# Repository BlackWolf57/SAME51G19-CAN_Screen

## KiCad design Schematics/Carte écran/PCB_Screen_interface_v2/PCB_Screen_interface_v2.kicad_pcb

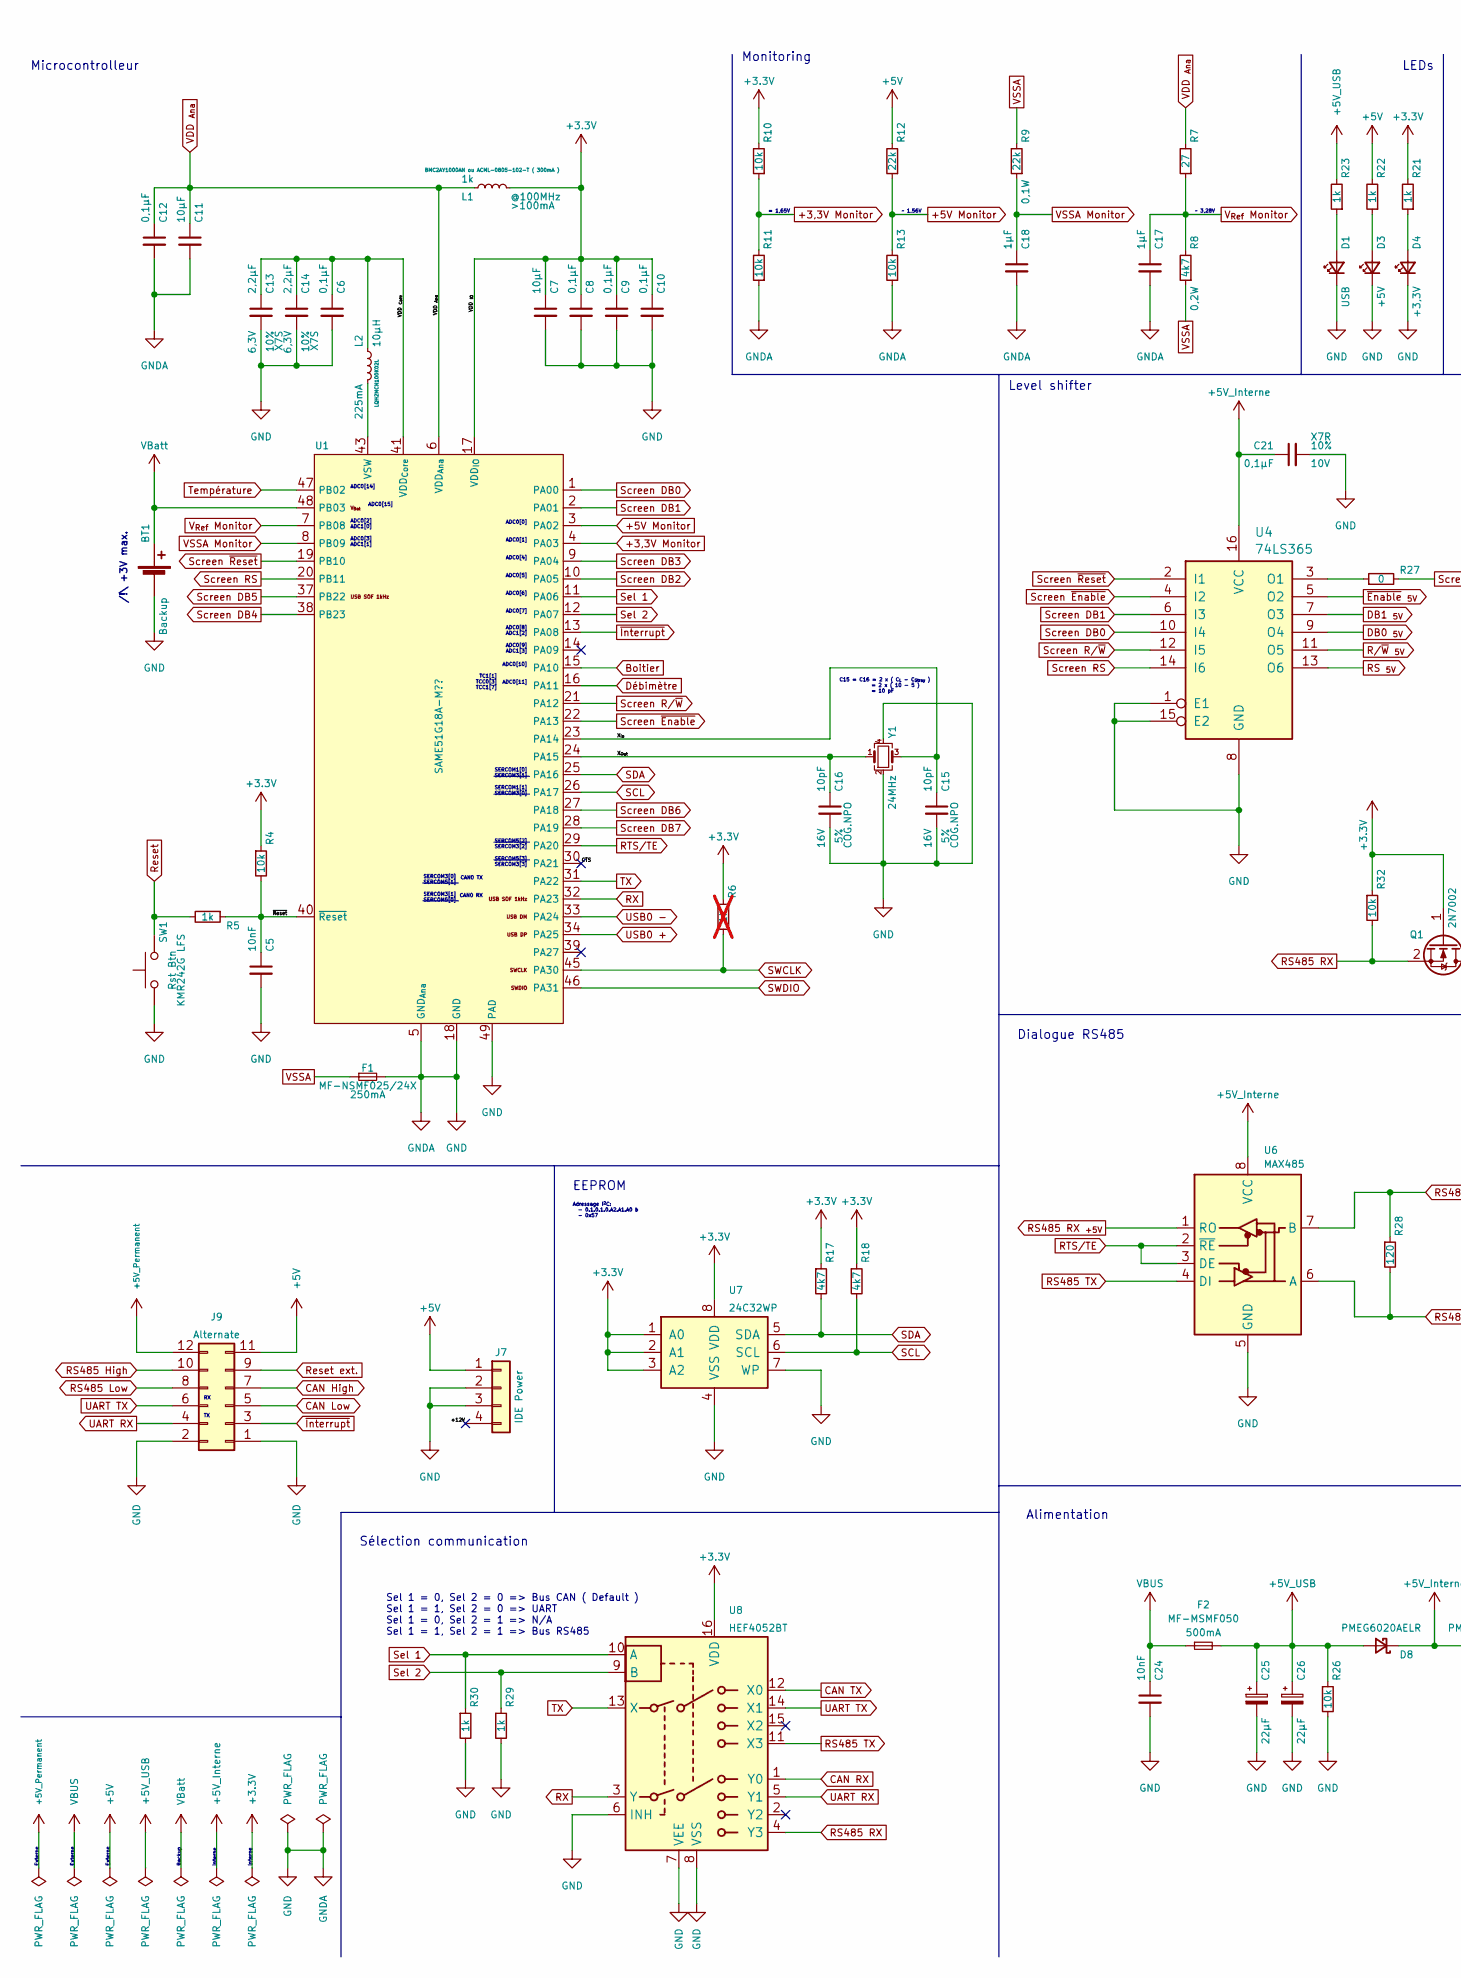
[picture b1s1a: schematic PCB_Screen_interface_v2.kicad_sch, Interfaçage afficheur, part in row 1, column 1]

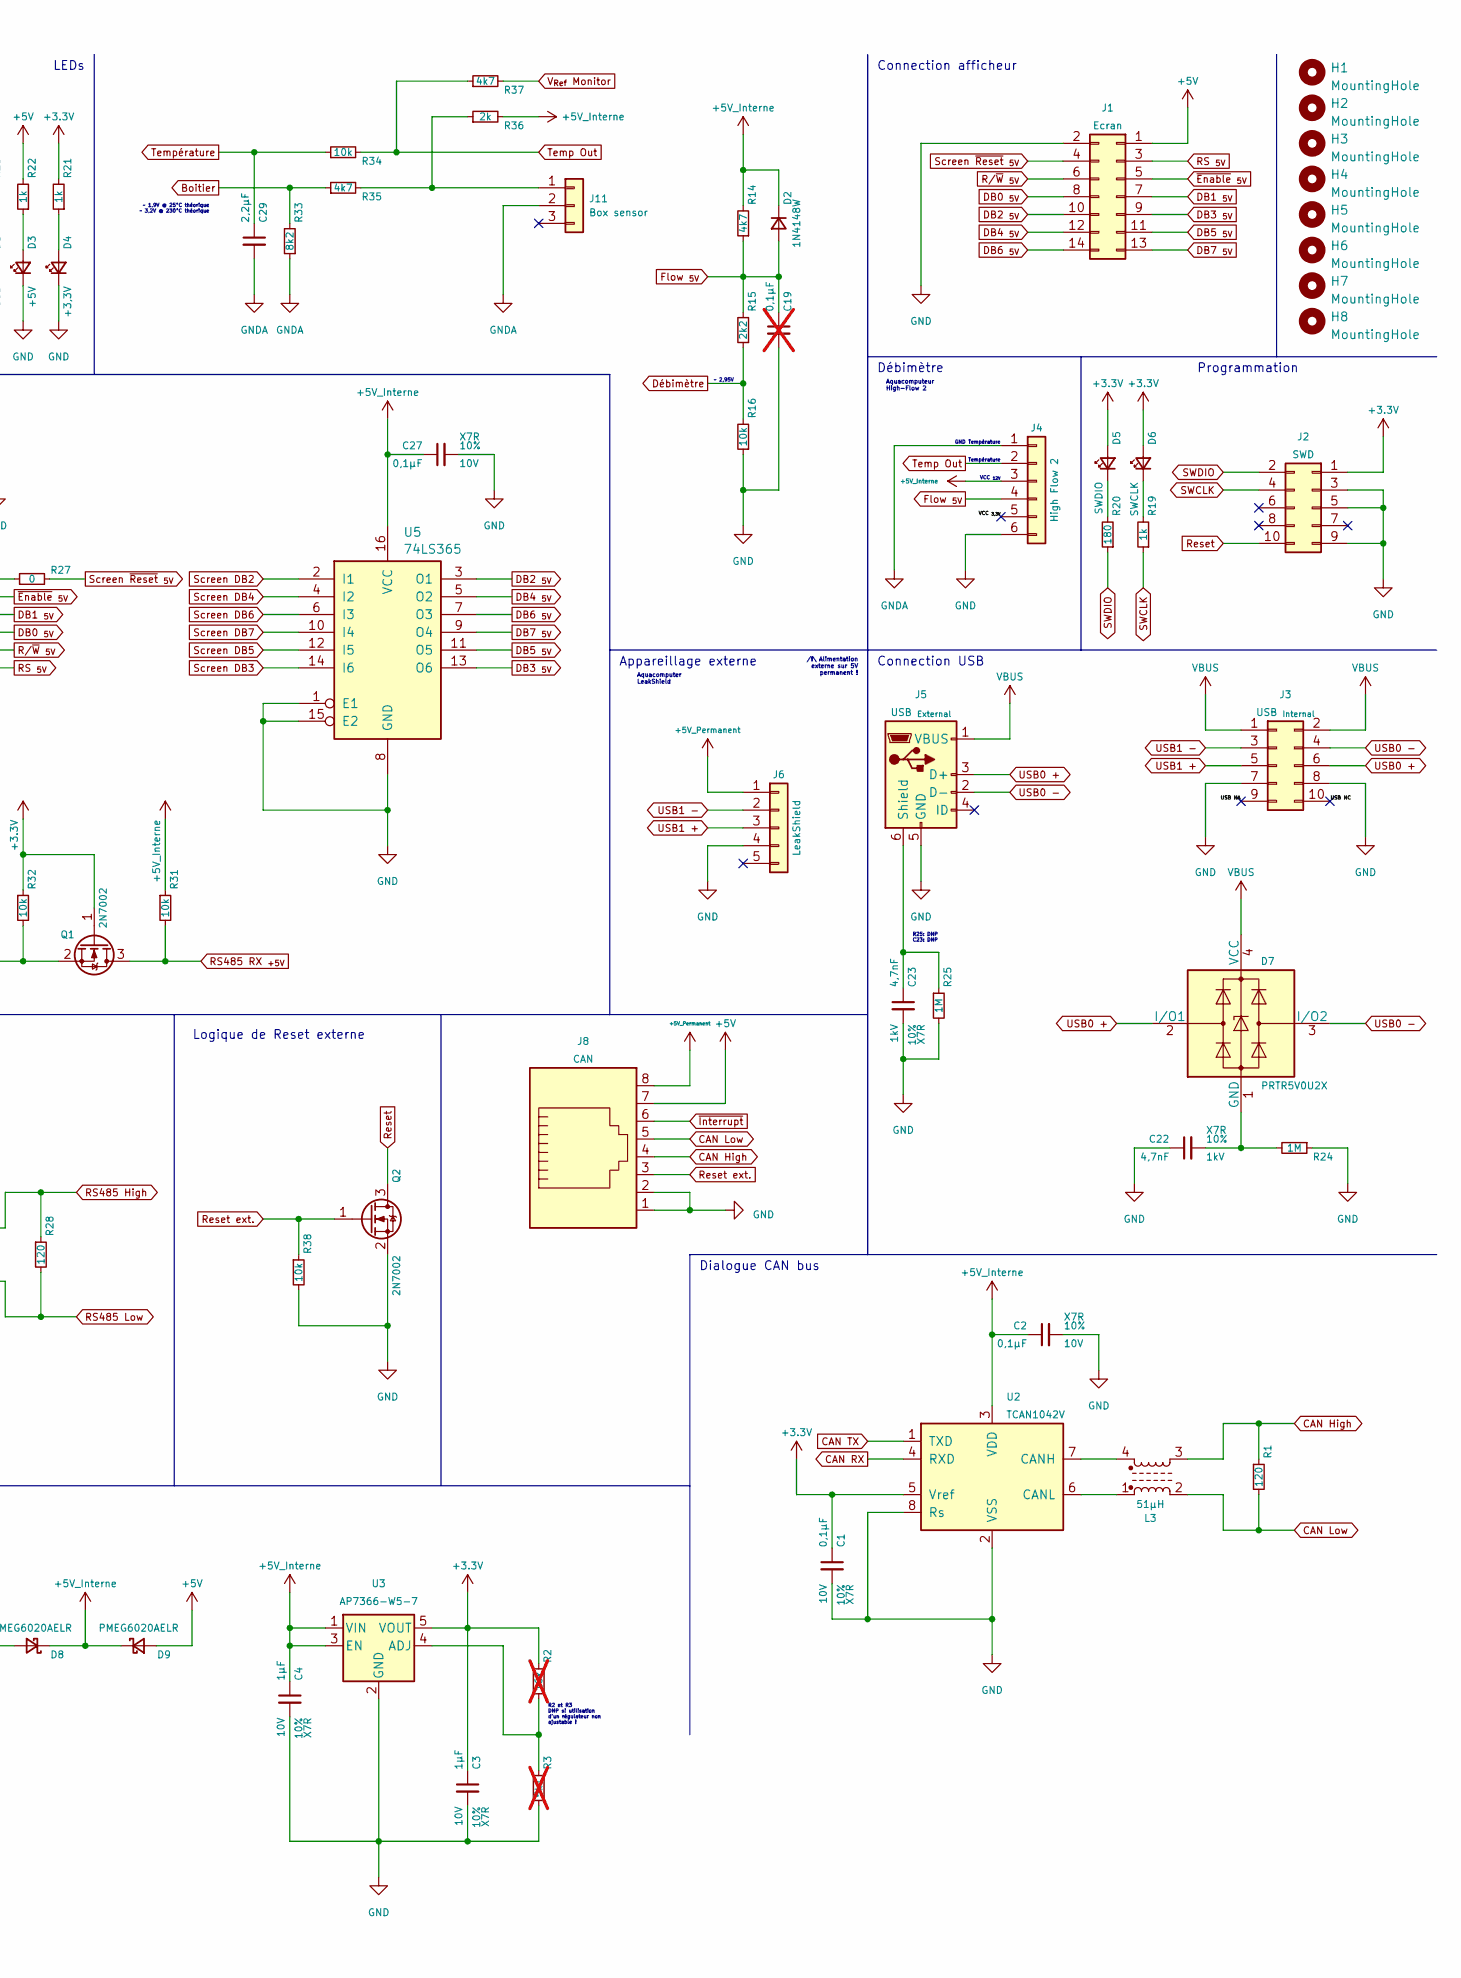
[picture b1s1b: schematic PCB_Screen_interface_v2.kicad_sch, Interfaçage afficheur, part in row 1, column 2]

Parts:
BT1: Backup; BatteryHolder_Keystone_106_1x20mm
C1, C2, C6, C8, C9, C10, C12, C21, C27: 0,1µF; C_0805_2012Metric
C3, C4, C17, C18: 1µF; C_0805_2012Metric
C5, C24: 10nF; C_0805_2012Metric
C7, C11: 10µF; C_0805_2012Metric
C13, C14, C29: 2,2µF; C_0805_2012Metric
C15, C16: 10pF; C_0805_2012Metric
C19: 0,1µF; C_0805_2012Metric; not fitted
C22, C23: 4,7nF; C_1206_3216Metric
C25, C26: 22µF; CP_Elec_4x5.8
D1: USB; LED_1206_3216Metric
D2: 1N4148W; D_SOD-123
D3: +5V; LED_1206_3216Metric_Pad1.42x1.75mm_HandSolder
D4: +3,3V; LED_1206_3216Metric_Pad1.42x1.75mm_HandSolder
D5: SWDIO; LED_1206_3216Metric
D6: SWCLK; LED_1206_3216Metric
D7: PRTR5V0U2X; SOT-143
D8, D9: PMEG6020AELR; Nexperia_CFP3_SOD-123W
F1: MF-NSMF025/24X; Fuse_1206_3216Metric
F2: MF-MSMF050; Fuse_1812_4532Metric
H1, H2, H3, H4, H5, H6, H7, H8: MountingHole; MountingHole_3.2mm_M3_DIN965
J1: Ecran; PinSocket_2x07_P2.54mm_Vertical
J2: SWD; PinHeader_2x05_P1.27mm_Vertical
J3: USB _{Internal}; IDC-Header_2x05_P2.54mm_Vertical
J4: High Flow 2; Molex_PicoBlade_53047-0610_1x06_P1.25mm_Vertical
J5: USB _{External}; Micro-USB
J6: LeakShield; Molex_PicoBlade_53047-0510_1x05_P1.25mm_Vertical
J7: IDE Power; Molex_4
J8: CAN; RJ45
J9: Alternate; IDC-Header_2x06_P2.54mm_Vertical
J11: Box sensor; Molex_PicoBlade_53047-0310_1x03_P1.25mm_Vertical
L1: 1k; L_0805_2012Metric
L2: 10µH; L_Murata_LQH2MCNxxxx02_2.0x1.6mm
L3: 51µH; Self_CAN
Q1, Q2: 2N7002; SOT-23
R1: 120; R_1206_3216Metric
R2: 16k; R_0805_2012Metric; not fitted
R3: 5k1; R_0805_2012Metric; not fitted
R4, R10, R11, R13, R16, R26, R31, R32, R34, R38: 10k; R_0805_2012Metric
R5, R19, R21, R22, R23, R29, R30: 1k; R_0805_2012Metric
R6: 1k; R_0805_2012Metric; not fitted
R7: 27; R_0805_2012Metric
R8: 4k7; R_1206_3216Metric
R9: 22k; R_1206_3216Metric
R12: 22k; R_0805_2012Metric
R14, R17, R18, R35, R37: 4k7; R_0805_2012Metric
R15: 2k2; R_0805_2012Metric
R20: 180; R_0805_2012Metric
R24, R25: 1M; R_0805_2012Metric
R27: 0; R_1206_3216Metric
R28: 120; R_0805_2012Metric
R33: 8k2; R_0805_2012Metric
R36: 2k; R_0805_2012Metric
SW1: Rst Btn; SW_Push_1P1T_NO_CK_KMR2
U1: SAME51G18A-M??; VQFN-48-1EP_7x7mm_P0.5mm_EP4.1x4.1mm
U2: TCAN1042V; SOIC-8_3.9x4.9mm_P1.27mm
U3: AP7366-W5-7; SOT-23-5
U4, U5: 74LS365; SOIC-16_3.9x9.9mm_P1.27mm
U6: MAX485; SOIC-8_3.9x4.9mm_P1.27mm
U7: 24C32WP; SOIC-8_3.9x4.9mm_P1.27mm
U8: HEF4052BT; SOIC-16_3.9x9.9mm_P1.27mm
Y1: 24MHz; Crystal_SMD_3225-4Pin_3.2x2.5mm

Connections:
+3,3V Monitor: R10.1, R11.2, U1.4 (PA03)
+3.3V: C1.1, C3.1, C7.1, C8.1, C9.1, C10.1, D5.2 (A), D6.2 (A), J2.1, L1.2, Q1.1 (G), R2.1, R4.1, R6.1, R10.2, R17.1, R18.1, R21.2, R32.1, U1.17 (VDD_{IO}), U1.36 (VDD_{IO}), U1.44 (VDD_{IO}), U2.5 (Vref), U3.5 (VOUT), U7.1 (A0), U7.2 (A1), U7.3 (A2), U7.8 (VDD), U8.16 (VDD)
+5V: D9.2 (A), J1.1, J7.1, J8.7, J9.11, R12.2, R22.2
+5V Monitor: R12.1, R13.2, U1.3 (PA02)
+5V_Interne: C2.1, C4.1, C21.1, C27.1, D2.1 (K), D8.1 (K), D9.1 (K), J4.3, R14.2, R31.1, R36.2, U2.3 (VDD), U3.1 (VIN), U3.3 (EN), U4.16 (VCC), U5.16 (VCC), U6.8 (VCC)
+5V_Permanent: J6.1, J8.8, J9.12
+5V_USB: C25.1, C26.1, D8.2 (A), F2.2, R23.2, R26.1
/+12V: J7.4
/CTS: U1.30 (PA21)
/USB NA: J3.9
/USB NC: J3.10
/VCC _{3,3V}: J4.5
/VDD _{Core}: C6.1, C13.1, C14.1, L2.1, U1.41 (VDD_{Core})
/X_{In}: C15.1, U1.23 (PA14), Y1.3
/X_{Out}: C16.1, U1.24 (PA15), Y1.1
/~Reset: C5.1, R4.2, R5.1, U1.40 (~Reset)
Boitier: R33.2, R35.1, U1.15 (PA10)
CAN High: J8.4, J9.7, L3.3, R1.1
CAN Low: J8.5, J9.5, L3.2, R1.2
CAN RX: U2.4 (RXD), U8.1 (Y0)
CAN TX: U2.1 (TXD), U8.12 (X0)
DB0 _{5V}: J1.8, U4.9 (O4)
DB1 _{5V}: J1.7, U4.7 (O3)
DB2 _{5V}: J1.10, U5.3 (O1)
DB3 _{5V}: J1.9, U5.13 (O6)
DB4 _{5V}: J1.12, U5.5 (O2)
DB5 _{5V}: J1.11, U5.11 (O5)
DB6 _{5V}: J1.14, U5.7 (O3)
DB7 _{5V}: J1.13, U5.9 (O4)
Débimètre: R15.1, R16.2, U1.16 (PA11)
Flow _{5V}: C19.1, D2.2 (A), J4.4, R14.1, R15.2
GND: BT1.2 (-), C1.2, C2.2, C3.2, C4.2, C5.2, C6.2, C7.2, C8.2, C9.2, C10.2, C11.2, C12.2, C13.2, C14.2, C15.2, C16.2, C17.2, C18.2, C19.2, C21.2, C22.1, C23.2, C24.2, C25.2, C26.2, C27.2, C29.2, D1.1 (K), D3.1 (K), D4.1 (K), F1.2, J1.2, J2.3, J2.5, J2.9, J3.7, J3.8, J4.1, J4.6, J5.5 (GND), J6.4, J7.2, J7.3, J8.1, J8.2, J9.1, J9.2, J11.2, Q2.2 (S), R3.2, R11.1, R13.1, R16.1, R24.1, R25.2, R26.2, R29.2, R30.2, R33.1, R38.2, SW1.1, U1.5 (GND_{Ana}), U1.18 (GND), U1.35 (GND), U1.42 (GND), U1.49 (PAD), U2.2 (VSS), U2.8 (Rs), U3.2 (GND), U4.1 (E1), U4.8 (GND), U4.15 (E2), U5.1 (E1), U5.8 (GND), U5.15 (E2), U6.5 (GND), U7.4 (VSS), U7.7 (WP), U8.6 (INH), U8.7 (VEE), U8.8 (VSS), Y1.2, Y1.4
unnamed: D1.2 (A), R23.1
unnamed: D3.2 (A), R22.1
unnamed: D4.2 (A), R21.1
unnamed: D5.1 (K), R20.2
unnamed: D6.1 (K), R19.2
unnamed: C22.2, D7.1 (GND), R24.2
unnamed: C23.1, J5.6 (Shield), R25.1
unnamed: J11.1, R35.2, R36.1
unnamed: L2.2, U1.43 (VSW)
unnamed: L3.4, U2.7 (CANH)
unnamed: L3.1, U2.6 (CANL)
unnamed: R2.2, R3.1, U3.4 (ADJ)
unnamed: R27.1, U4.3 (O1)
RS485 High: J9.10, R28.1, U6.7 (B)
RS485 Low: J9.8, R28.2, U6.6 (A)
RS485 RX: Q1.2 (S), R32.2, U8.4 (Y3)
RS485 RX _{+5V}: Q1.3 (D), R31.2, U6.1 (RO)
RS485 TX: U6.4 (DI), U8.11 (X3)
RS _{5V}: J1.3, U4.13 (O6)
RTS/TE: U1.29 (PA20), U6.2 (~RE), U6.3 (DE)
RX: U1.32 (PA23), U8.3 (Y)
Reset: J2.10, Q2.3 (D), R5.2, SW1.2
Reset ext.: J8.3, J9.9, Q2.1 (G), R38.1
R/~W _{5V}: J1.6, U4.11 (O5)
SCL: R18.2, U1.26 (PA17), U7.6 (SCL)
SDA: R17.2, U1.25 (PA16), U7.5 (SDA)
SWCLK: J2.4, R6.2, R19.1, U1.45 (PA30)
SWDIO: J2.2, R20.1, U1.46 (PA31)
Screen DB0: U1.1 (PA00), U4.10 (I4)
Screen DB1: U1.2 (PA01), U4.6 (I3)
Screen DB2: U1.10 (PA05), U5.2 (I1)
Screen DB3: U1.9 (PA04), U5.14 (I6)
Screen DB4: U1.38 (PB23), U5.4 (I2)
Screen DB5: U1.37 (PB22), U5.12 (I5)
Screen DB6: U1.27 (PA18), U5.6 (I3)
Screen DB7: U1.28 (PA19), U5.10 (I4)
Screen RS: U1.20 (PB11), U4.14 (I6)
Screen R/~W: U1.21 (PA12), U4.12 (I5)
Screen ~Enable: U1.22 (PA13), U4.4 (I2)
Screen ~Reset: U1.19 (PB10), U4.2 (I1)
Screen ~Reset _{5V}: J1.4, R27.2
Sel 1: R30.1, U1.11 (PA06), U8.10 (A)
Sel 2: R29.1, U1.12 (PA07), U8.9 (B)
TX: U1.31 (PA22), U8.13 (X)
Temp Out: J4.2, R34.2, R37.1
Température: C29.1, R34.1, U1.47 (PB02)
UART RX: J9.4, U8.5 (Y1)
UART TX: J9.6, U8.14 (X1)
USB0 +: D7.2 (I/O1), J3.6, J5.3 (D+), U1.34 (PA25)
USB0 -: D7.3 (I/O2), J3.4, J5.2 (D-), U1.33 (PA24)
USB1 +: J3.5, J6.3
USB1 -: J3.3, J6.2
VBUS: C24.1, D7.4 (VCC), F2.1, J3.1, J3.2, J5.1 (VBUS)
VBatt: BT1.1 (+), U1.48 (PB03)
VDD _{Ana}: C11.1, C12.1, L1.1, R7.2, U1.6 (VDD_{Ana})
VSSA: F1.1, R8.1, R9.2
VSSA Monitor: C18.1, R9.1, U1.8 (PB09)
V_{Ref} Monitor: C17.1, R7.1, R8.2, R37.2, U1.7 (PB08)
~Enable _{5V}: J1.5, U4.5 (O2)
~Interrupt: J8.6, J9.3, U1.13 (PA08)

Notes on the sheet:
ADC0[10]
SERCOM3[0] SERCOM5[1]
ADC0[3] ADC1[1]
ADC0[9] ADC1[3]
~ 3,28V
Connection afficheur
LEDs
Débimètre
SERCOM1[1] SERCOM3[0]
SERCOM5[2] SERCOM3[2]
GND Température
= 1,65V
EEPROM
Externe
ADC0[2] ADC1[0]
CAN0 RX
ADC0[4]
Level shifter
Dialogue CAN bus
Alimentation
Adressage I^{2}C: - 0.1.0.1.0.A2.A1.A0 b - 0x57
Appareillage externe
Interne
Backup
Monitoring
ADC0[14]
~ 1,9V @ 25°C théorique ~ 3,2V @ 230°C théorique
Sélection communication
ADC0[7]
CAN0 TX
Programmation
ADC0[1]
/!\ Alimentation externe sur 5V permanent !
R25: DNP C23: DNP
/!\ +3V max.
C15 = C16 = 2 x ( C_{L} - C_{Stray} ) = 2 x ( 10 - 5 ) = 10 pF
Microcontrolleur
ADC0[15]
TC1[1] TCC0[3] TCC1[7]
ADC0[6]

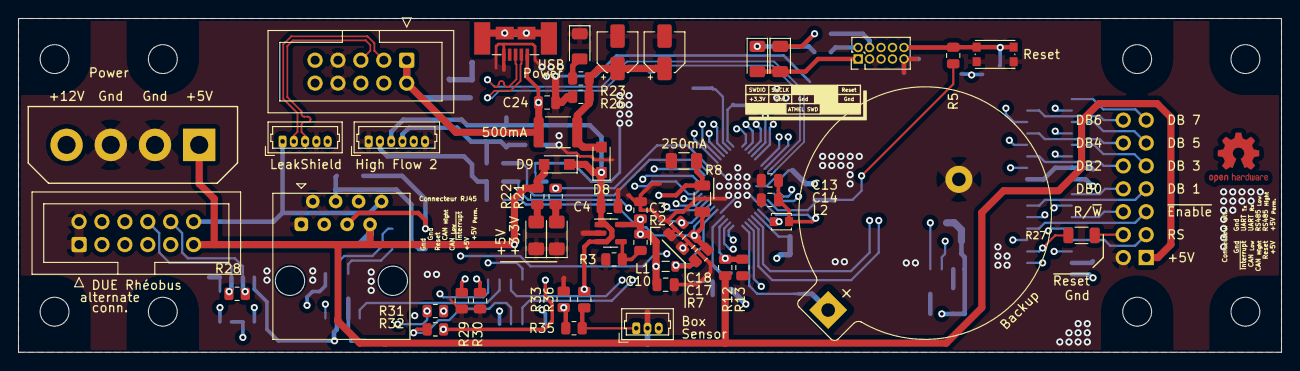
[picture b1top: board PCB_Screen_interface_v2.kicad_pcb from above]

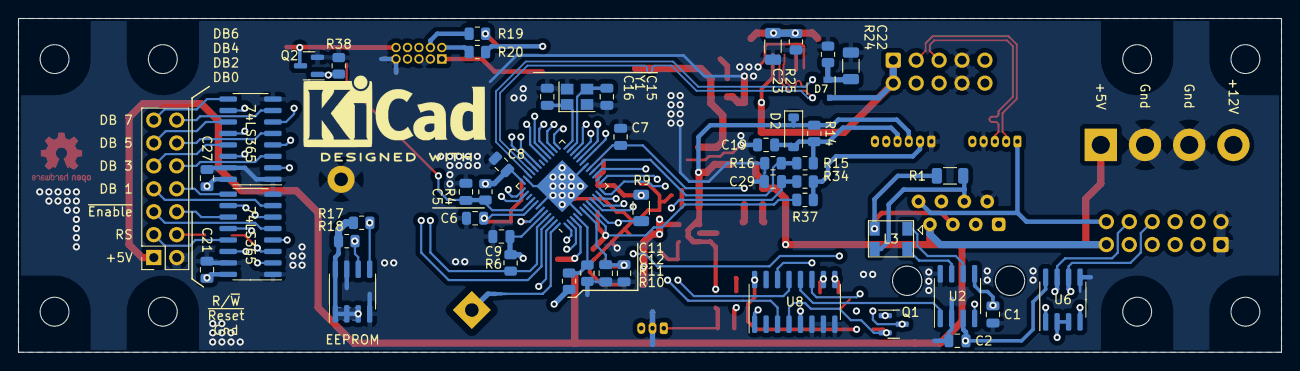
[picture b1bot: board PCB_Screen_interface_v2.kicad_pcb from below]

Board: 4 copper layers, 140.0 x 37.0 mm, 110 parts (49 on the bottom side), 87 nets.
